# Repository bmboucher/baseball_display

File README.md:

# baseball_display

A pygame-based MLB scoreboard for a three-panel "jumbotron." Each panel is
480×320; combined they show a live scoreboard, batting order / player
stats, and a field diagram with runner/defender badges.

Two render targets are supported from the same codebase:

- **Desktop**: a single 1440×320 pygame window (three panels side by side).
- **Raspberry Pi**: three physical ST7796S SPI displays, driven from one
  process via a pure-Python SPI driver. See [`PI_SETUP.md`](PI_SETUP.md)
  for the full hardware setup (wiring, kernel config, systemd unit,
  nightly auto-update cron).

## Quick start (desktop)

```bash
cd baseball_display          # must run from inside the project directory
python3 -m venv .venv
source .venv/bin/activate    # or .\.venv\Scripts\Activate.ps1 on Windows
pip install -e .
python -m baseball_display
```

> Run these (and `python -m baseball_display`) from inside the
> `baseball_display/` project directory. From any parent directory,
> Python's import machinery resolves `baseball_display` as a namespace
> package pointing at the project folder itself and bypasses the
> editable install, producing a confusing `ImportError` like
> `cannot import name 'make_endpoint' from 'baseball_display.cache'`.

The UI font is bundled (Fira Code) so desktop and Pi render identically.

`settings.json` (in the working directory) holds runtime config. Set the
path via the `BASEBALL_DISPLAY_SETTINGS` env var. Missing file ⇒ defaults.

```jsonc
{
  "refresh_rate": 10,          // seconds between MLB API polls
  "multi_process": false,      // see "Multi-process mode" below
  "startup_team": "NYM"        // team abbreviation used to pick the initial game/mode at boot
}
```

## Running modes

`baseball_display.app.main()` picks one of three render paths at startup:

| Condition                                       | Path                       | What you see                                     |
|-------------------------------------------------|----------------------------|--------------------------------------------------|
| `multi_process=false` (default)                 | `_run_single_process`      | One 1440×320 pygame window                       |
| `multi_process=true` **and** on a Pi            | `_run_pi_panels`           | Three ST7796S SPI panels (headless, no window)   |
| `multi_process=true` **and** not on a Pi        | `_run_multi_process`       | A small "control" window + three 480×320 windows |

Detection is `import RPi.GPIO` — succeeds when `rpi-lgpio` is installed
(Pi only). Override the flag from the shell with
`BASEBALL_DISPLAY_MULTI_PROCESS=1`.

## Architecture

### Three-panel layout

```
┌──────────────────────────┬──────────────────────────┬──────────────────────────┐
│      LeftJumbotron       │      RightJumbotron      │         Diamond          │
│         480×320          │         480×320          │         480×320          │
└──────────────────────────┴──────────────────────────┴──────────────────────────┘
   x=0, y=0                   x=480                       x=960
```

Each panel is a `ScreenBuffer` (in `screens.py`). Components are yielded
per current `DisplayMode`:

| Mode          | LeftJumbotron                                         | RightJumbotron       | Diamond                       |
|---------------|-------------------------------------------------------|----------------------|-------------------------------|
| `MAIN_MENU`   | `MainMenu`                                            | (blank)              | field diagram (no overlays)   |
| `GAME_SELECT` | `GameSelect`                                          | `GamePreview`        | field diagram (no overlays)   |
| `PREVIEW`     | `GameCountdown`                                       | `GamePreview`        | field diagram (no overlays)   |
| `LIVE` / `REPLAY` | `Scoreboard`, `PitchDisplay`, `PAEvents`, `CountDisplay`, `ClockDisplay` | `BattingOrder`  | field + runner/defender/pitch overlays |
| `SETTINGS`    | `SettingsMenu`                                        | (blank)              | field diagram (no overlays)   |
| `PLAYERS`     | `PlayerSelect`                                        | `PlayerStatsPanel`   | field diagram (no overlays)   |

### Pi single-process render path

On the Pi we render to three off-screen pygame Surfaces (with
`SDL_VIDEODRIVER=dummy`, no real display) and push pixels via SPI:

1. `pygame.init()` once, dummy display.
2. Reset the panels (shared RST line pulsed once).
3. Send the ST7796S init sequence to each panel (CSCON unlock + gamma +
   MADCTL/COLMOD); see [`baseball_display/st7796s.py`](baseball_display/st7796s.py).
4. Main loop (≤30 FPS): poll encoders, `state.update_state()`, render
   each `ScreenBuffer` to its 480×320 surface, push pixels through the
   dirty-rectangle SPI driver.

The ST7796S driver tracks the previously-pushed RGB888 bytes per panel
and ships only the bounding box of changed pixels (RGB565 BE, chunked
to `spidev.bufsiz`). For mostly-static panels (scoreboard, batting
order) this means most frames skip SPI entirely; for the diamond's
runner animation, only the animation path is pushed.

### Desktop multi-process path

Used only for debugging the IPC + dirty-rect logic on a workstation.
Parent process owns input + MLB HTTP + State; three spawned children
each open a visible 480×320 pygame window. The parent publishes a
pickled `(DisplayData, State)` snapshot to a Manager namespace whenever
state changes; children pull on a shared version-counter bump. See
[`baseball_display/multiproc.py`](baseball_display/multiproc.py).

## Input

| Encoder            | Switch     | Rotate                     | Key emitted                |
|--------------------|------------|----------------------------|----------------------------|
| X (left)           | GPIO 24    | GPIO 22 (DT) + 23 (CLK)    | LEFT/RIGHT + SPACE (back)  |
| Y (right)          | GPIO 17    | GPIO 27 (DT) + 18 (CLK)    | UP/DOWN + ENTER (select)   |

`pi_input.PiInputAdapter` injects `pygame.KEYDOWN` events so the desktop
keyboard path and Pi encoder path use the same `state.handle_event`
dispatcher.

Mode transitions:

- `MAIN_MENU` → (Enter on "Games") → `GAME_SELECT`
- `MAIN_MENU` → (Enter on "Player Stats") → `PLAYERS`
- `MAIN_MENU` → (Enter on "Settings") → `SETTINGS`
- `GAME_SELECT` → (Enter) → `REPLAY` / `LIVE` / `PREVIEW` (depending on tab)
- Any submode → (Space) → back one level

## State model

All mutable state lives in `state.py` as Pydantic v2 models. Components
read state only via module-level accessor functions; **components must
never call `get_game_data()` or touch raw `GameFeed` objects** — all
display-derived data must live on `DisplayData` and be populated inside
`DisplayData.observe_game()`. The play-by-play replay engine is the only
thing that walks the live feed.

Module-level globals (`state.py`):

| Global                  | Type                | Set by                          |
|-------------------------|---------------------|---------------------------------|
| `_state`                | `State`             | `handle_event` mutations, `update_state` |
| `_game_data`            | `GameFeed \| None`  | `update_state` (refresh tick)   |
| `_game_data_parsed`     | `_GameData \| None` | `update_state`                  |
| `_game_display_data`    | `DisplayData`       | `DisplayData.observe_game`      |
| `_dirty`                | `bool`              | `handle_event`, `update_state` (consumed in multi-process for snapshot publish) |

The multi-process desktop path also uses `set_state` / `set_game_display_data`
setters to install pickled snapshots in render children — the
single-process and Pi paths use the in-place mutation directly.

## How to add a component

1. Create `baseball_display/components/my_component.py`. Subclass
   `Component` (override `draw(surface)`) or `ValueComponent` (override
   `get_value()` and `render_value(value)` — the base class caches the
   rendered surface and re-renders only when the value changes).
2. Re-export from `baseball_display/components/__init__.py`.
3. Read state with `get_game_display_data()` / `get_state()`. Pull
   constants from `display_constants.py`; don't hardcode geometry/colors.
4. Instantiate inside the relevant `ScreenBuffer` subclass in
   `screens.py` and yield it from `get_active_components(mode)`.

## How to add a display mode

1. Add a variant to `DisplayMode` in `state.py`.
2. Add the corresponding sub-state model and wire it into `State`.
3. Add `handle_scroll_x/y` and `handle_click_x/y` branches in `State`.
4. Add an `elif mode == DisplayMode.NEW_MODE:` branch in each relevant
   `ScreenBuffer.get_active_components()`.

## Project layout

```
baseball_display/
  app.py              # entrypoint; picks render path
  state.py            # all state models + DisplayMode + handle_event
  screens.py          # ScreenBuffer subclasses; build_screen() factory
  components/         # one file per UI component
  st7796s.py          # pure-Python ST7796S SPI driver (Pi only)
  multiproc.py        # desktop multi-process debug renderer
  pi_input.py         # rotary-encoder → pygame.KEYDOWN adapter
  statsapi.py         # caching, rate-limited MLB Stats API wrapper
  mlb_api/            # generated Pydantic models + JSON schemas
  display_constants.py# geometry, colors, font sizes
  settings.py         # Settings (refresh_rate, multi_process, panels)
  logging_setup.py    # shared dictConfig
scripts/
  build_schemas.py            # regenerate JSON schemas from sample responses
  regenerate_models.py        # regenerate Pydantic models from schemas
  patch_live_game_schema.py   # post-process patches for the live_game schema
  panel_test.py               # Pi bench test: cycle each panel through solid colors
  update_and_restart.sh       # nightly self-update (called by cron)
  verify_encoders.py          # standalone encoder diagnostic
PI_SETUP.md           # full Pi setup (hardware, OS, systemd, cron)
```

## Tests / Development

There is **no automated test suite**. `test_observe.py` and
`test_pitches.py` at the project root are live-endpoint debug scripts —
they hit `statsapi.mlb.com` and `print()` results, with no assertions.
Don't run them under `pytest` and don't count them as a "test pass."

## Dependencies

| Package          | Purpose                                          | When required           |
|------------------|--------------------------------------------------|-------------------------|
| `pygame`         | Rendering, fonts, event loop                     | Always                  |
| `pydantic`       | State models, JSON validation                    | Always                  |
| `MLB-StatsAPI`   | MLB API client                                   | Always                  |
| `rpi-lgpio`      | `RPi.GPIO`-compatible GPIO on modern Pi kernels  | Pi (`[raspberry-pi]`)   |
| `spidev`         | SPI bus access                                   | Pi (`[raspberry-pi]`)   |
| `numpy`          | RGB888 → RGB565 conversion + dirty-rect diff     | Pi (`[raspberry-pi]`)   |

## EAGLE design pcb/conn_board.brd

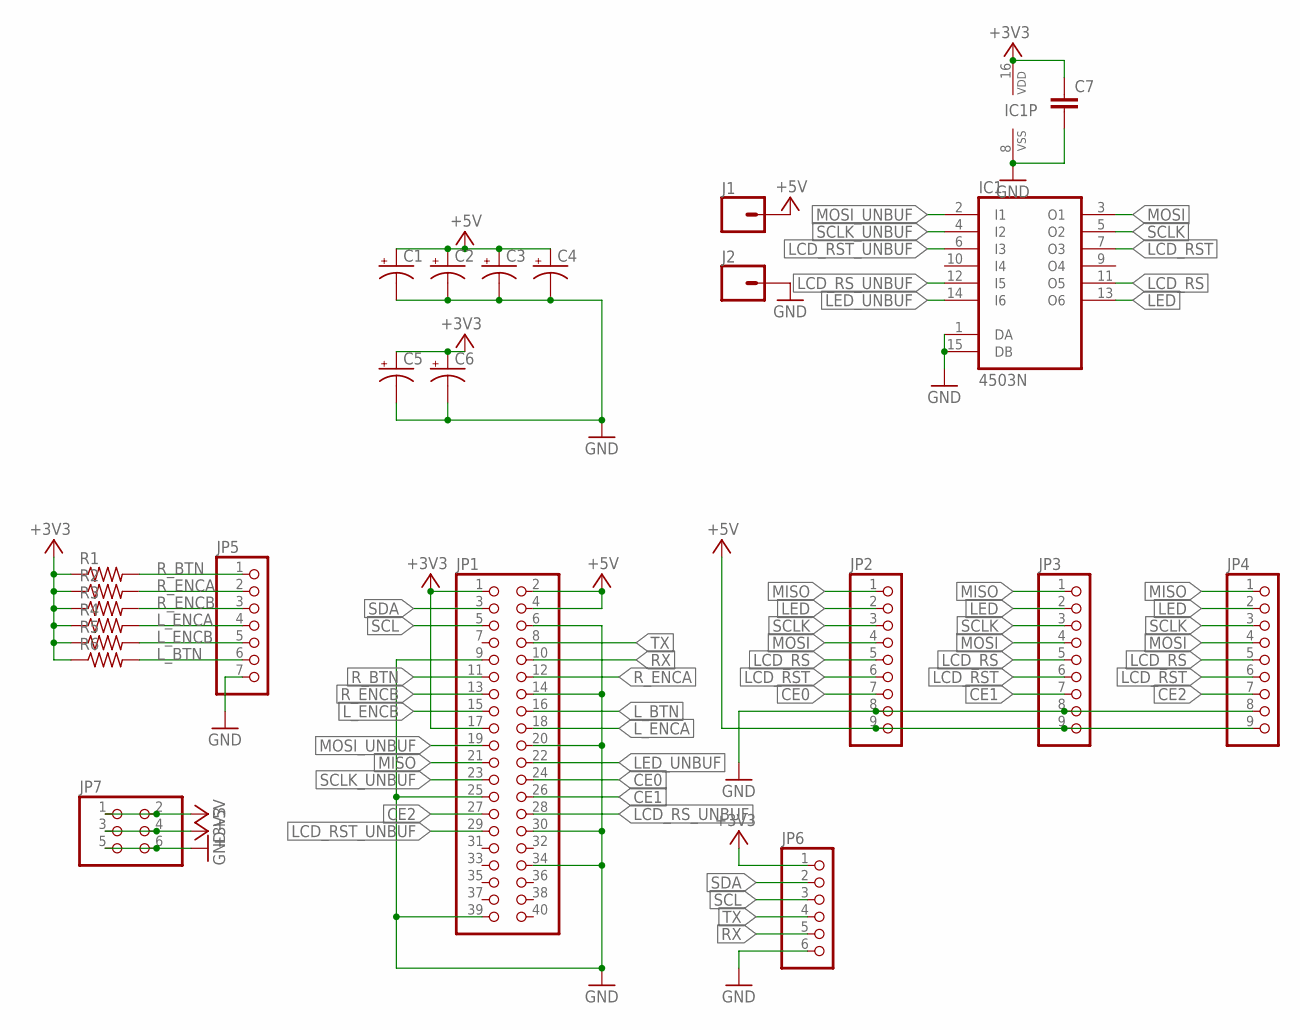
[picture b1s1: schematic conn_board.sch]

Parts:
C1, C2, C3, C4, C5, C6: CPOL-USSANYO_F13; SANYO-OSCON_F13
C7: C-EU050-055X075; C050-055X075
IC1: 4503N; DIL16
J1, J2: CONN_01PTH_LONGPAD; 1X01_LONGPAD
JP1: PINHD-2X20; 2X20
JP2, JP3, JP4: PINHD-1X9; 1X09
JP5: PINHD-1X7; 1X07
JP6: PINHD-1X6; 1X06
JP7: PINHD-2X3; 2X03
R1, R2, R3, R4, R5, R6: R-US_0207/10; 0207/10

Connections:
+3V3: C5.+, C6.+, C7.1, IC1.16 (VDD), JP1.1, JP1.17, JP6.1, JP7.3, JP7.4, R1.1, R2.1, R3.1, R4.1, R5.1, R6.1
+5V: C1.+, C2.+, C3.+, C4.+, J1.1, JP1.2, JP1.4, JP2.9, JP3.9, JP4.9, JP7.1, JP7.2
CE0: JP1.24, JP2.7
CE1: JP1.26, JP3.7
CE2: JP1.27, JP4.7
GND: C1.-, C2.-, C3.-, C4.-, C5.-, C6.-, C7.2, IC1.1 (DA), IC1.8 (VSS), IC1.15 (DB), J2.1, JP1.6, JP1.9, JP1.14, JP1.20, JP1.25, JP1.30, JP1.34, JP1.39, JP2.8, JP3.8, JP4.8, JP5.7, JP6.6, JP7.5, JP7.6
LCD_RS: IC1.11 (O5), JP2.5, JP3.5, JP4.5
LCD_RST: IC1.7 (O3), JP2.6, JP3.6, JP4.6
LCD_RST_UNBUF: IC1.6 (I3), JP1.29
LCD_RS_UNBUF: IC1.12 (I5), JP1.28
LED: IC1.13 (O6), JP2.2, JP3.2, JP4.2
LED_UNBUF: IC1.14 (I6), JP1.22
L_BTN: JP1.16, JP5.6, R6.2
L_ENCA: JP1.18, JP5.4, R4.2
L_ENCB: JP1.15, JP5.5, R5.2
MISO: JP1.21, JP2.1, JP3.1, JP4.1
MOSI: IC1.3 (O1), JP2.4, JP3.4, JP4.4
MOSI_UNBUF: IC1.2 (I1), JP1.19
RX: JP1.10, JP6.5
R_BTN: JP1.11, JP5.1, R1.2
R_ENCA: JP1.12, JP5.2, R2.2
R_ENCB: JP1.13, JP5.3, R3.2
SCL: JP1.5, JP6.3
SCLK: IC1.5 (O2), JP2.3, JP3.3, JP4.3
SCLK_UNBUF: IC1.4 (I2), JP1.23
SDA: JP1.3, JP6.2
TX: JP1.8, JP6.4

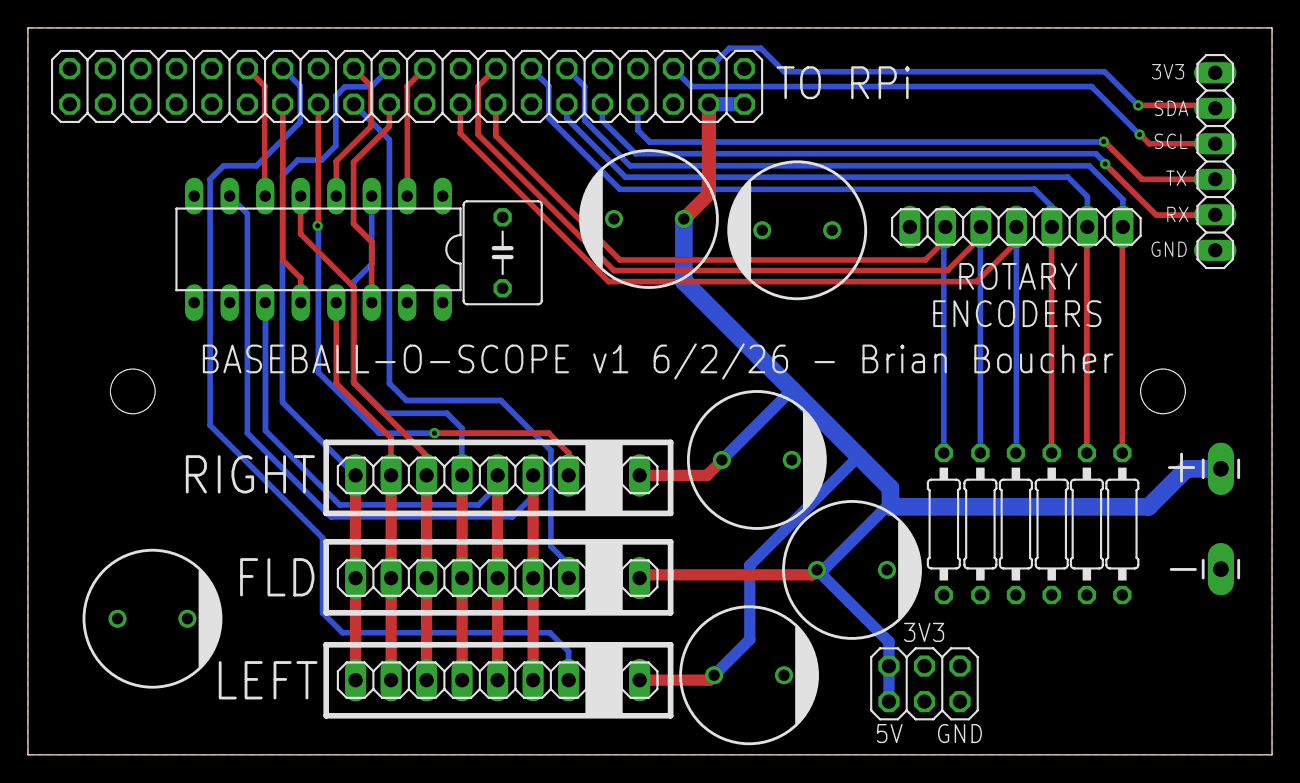
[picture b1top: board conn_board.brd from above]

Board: 2 copper layers, 89.0 x 52.0 mm, 23 parts (0 on the bottom side), 27 nets.

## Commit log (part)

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2026-05-10 Adding fonts
2026-05-10 Updating
2026-05-10 Adding rotary encoder control
2026-05-10 Adding rotary encoder control (take 2)
2026-05-10 Demoting file cache logs
2026-05-10 Try this
2026-05-14 Updates 5-14
2026-05-16 Updating with wifi
2026-06-17 Adding pcb
2026-06-17 Updated with debug logging
2026-06-17 Switching left encoder
2026-06-17 Fixing encoders

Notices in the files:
parts and their libraries:
SparkFun-Connectors: Licensing: Creative Commons ShareAlike 4.0 International - https://creativecommons.org/licenses/by-sa/4.0
